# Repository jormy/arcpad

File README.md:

# arcpad

arcpad is a 11 key macropad with a rotary enccoder and a light bar.
made for Hack Club's Stardance Hackpad program.

## features

- snap fit 3d printed case with no screws needed
- 11 keys in a 4x3 layout
- EC11 rotary encoder
- light bar composed of 5 LEDS that can be programmed to show whatever you want (e.g. volume, brightness)
- QMK firmware with VIA support (not tested yet)

## CAD model

I wanted to keep the design really compact, so I decided not to use screws and secured the PCB with friction instead.

The PCB is sandwiched between a base and a top plate, the PCB is secured to the top plate when the switches are attached, and the top plate secures to the base with some neat snap fit geometry

All parts of the model are printable with no supports, with exception of the USB-C opening in the base.

## PCB

here are the schematic andn PCB designs, both made in Kicad:

## Firmware

This macropad uses QMK firmware. It has VIA support, though I will need to test it when I make the physical macropad.

## BOM

everything you need to make this macropad

- 11x Cherry MX Switches
- 11x DSA Keycaps
- 12x through-hole 1N4148 Diodes
- 16x SK6812 MINI-E LEDs
- 1x EC11 Rotary encoder
- 1x XIAO RP2040
- 1x 100 µF capacitor
- 1x 330Ω resistor
- 1x Case (3 3d printed parts)

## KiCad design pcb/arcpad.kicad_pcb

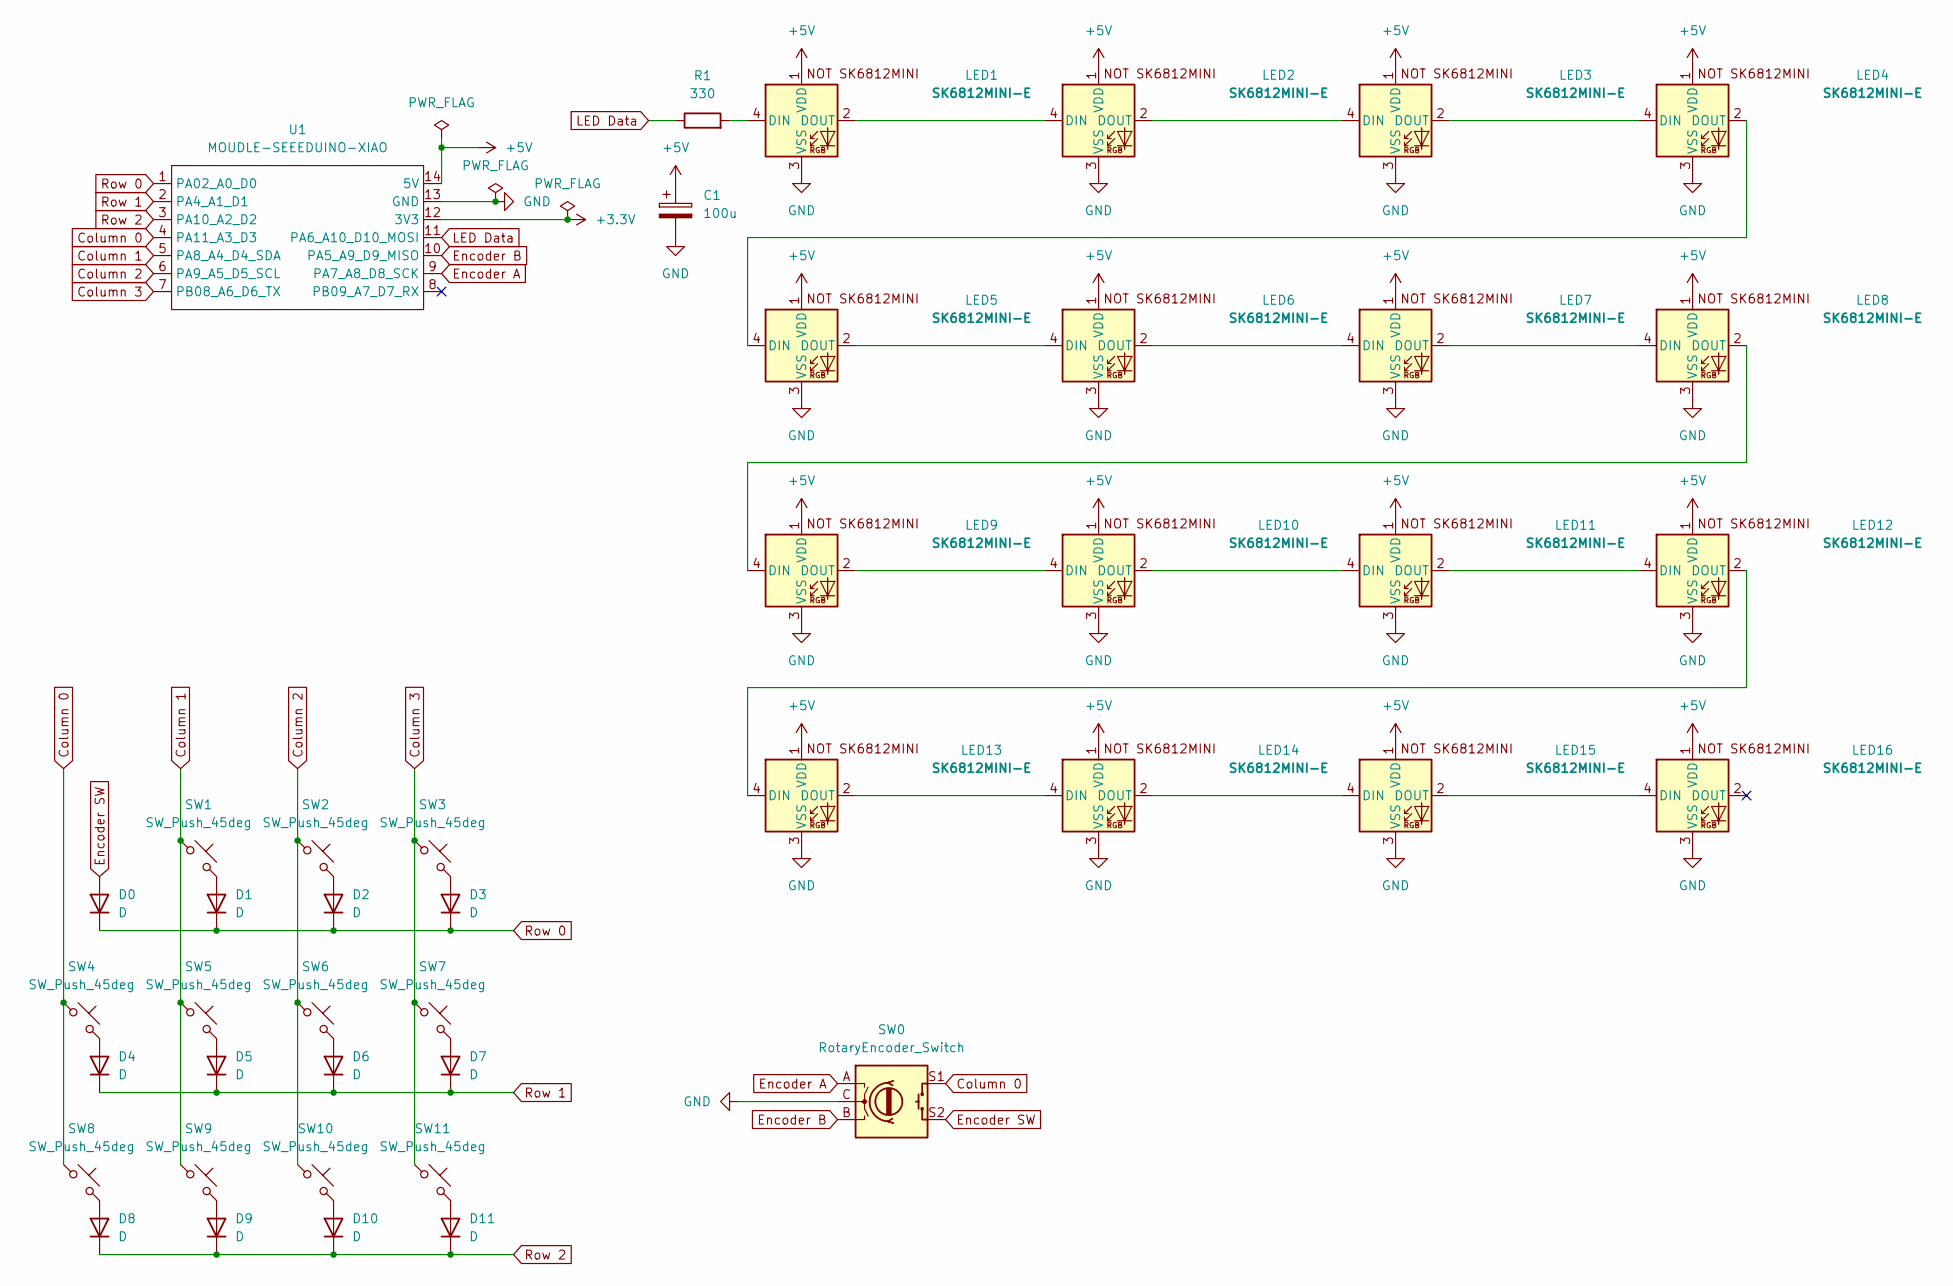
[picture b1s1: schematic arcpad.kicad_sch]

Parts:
C1: 100u; CP_Radial_D5.0mm_P2.00mm
D0, D1, D2, D3, D4, D5, D6, D7, D8, D9, D10, D11: D; D_DO-35_SOD27_P7.62mm_Horizontal
LED1, LED2, LED3, LED4, LED5, LED6, LED7, LED8, LED9, LED10, LED11, LED12, LED13, LED14, LED15, LED16: SK6812MINI-E; SK6812MINI-E_fixed
R1: 330; R_Axial_DIN0207_L6.3mm_D2.5mm_P7.62mm_Horizontal
SW0: RotaryEncoder_Switch; RotaryEncoder_Alps_EC11E-Switch_Vertical_H20mm
SW1, SW2, SW3, SW4, SW5, SW6, SW7, SW8, SW9, SW10, SW11: SW_Push_45deg; SW_Cherry_MX_1.00u_PCB
U1: MOUDLE-SEEEDUINO-XIAO; XIAO-Generic-Hybrid-14P-2.54-21X17.8MM

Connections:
+3.3V: U1.12 (3V3)
+5V: C1.1, LED1.1 (VDD), LED2.1 (VDD), LED3.1 (VDD), LED4.1 (VDD), LED5.1 (VDD), LED6.1 (VDD), LED7.1 (VDD), LED8.1 (VDD), LED9.1 (VDD), LED10.1 (VDD), LED11.1 (VDD), LED12.1 (VDD), LED13.1 (VDD), LED14.1 (VDD), LED15.1 (VDD), LED16.1 (VDD), U1.14 (5V)
Column 0: SW0.S1, SW4.1, SW8.1, U1.4 (PA11_A3_D3)
Column 1: SW1.1, SW5.1, SW9.1, U1.5 (PA8_A4_D4_SDA)
Column 2: SW2.1, SW6.1, SW10.1, U1.6 (PA9_A5_D5_SCL)
Column 3: SW3.1, SW7.1, SW11.1, U1.7 (PB08_A6_D6_TX)
Encoder A: SW0.A, U1.9 (PA7_A8_D8_SCK)
Encoder B: SW0.B, U1.10 (PA5_A9_D9_MISO)
Encoder SW: D0.2 (A), SW0.S2
GND: C1.2, LED1.3 (VSS), LED2.3 (VSS), LED3.3 (VSS), LED4.3 (VSS), LED5.3 (VSS), LED6.3 (VSS), LED7.3 (VSS), LED8.3 (VSS), LED9.3 (VSS), LED10.3 (VSS), LED11.3 (VSS), LED12.3 (VSS), LED13.3 (VSS), LED14.3 (VSS), LED15.3 (VSS), LED16.3 (VSS), SW0.C, U1.13 (GND)
LED Data: R1.1, U1.11 (PA6_A10_D10_MOSI)
unnamed: D1.2 (A), SW1.2
unnamed: D2.2 (A), SW2.2
unnamed: D3.2 (A), SW3.2
unnamed: D4.2 (A), SW4.2
unnamed: D5.2 (A), SW5.2
unnamed: D6.2 (A), SW6.2
unnamed: D7.2 (A), SW7.2
unnamed: D8.2 (A), SW8.2
unnamed: D9.2 (A), SW9.2
unnamed: D10.2 (A), SW10.2
unnamed: D11.2 (A), SW11.2
unnamed: LED1.4 (DIN), R1.2
unnamed: LED1.2 (DOUT), LED2.4 (DIN)
unnamed: LED2.2 (DOUT), LED3.4 (DIN)
unnamed: LED3.2 (DOUT), LED4.4 (DIN)
unnamed: LED4.2 (DOUT), LED5.4 (DIN)
unnamed: LED5.2 (DOUT), LED6.4 (DIN)
unnamed: LED6.2 (DOUT), LED7.4 (DIN)
unnamed: LED7.2 (DOUT), LED8.4 (DIN)
unnamed: LED8.2 (DOUT), LED9.4 (DIN)
unnamed: LED9.2 (DOUT), LED10.4 (DIN)
unnamed: LED10.2 (DOUT), LED11.4 (DIN)
unnamed: LED11.2 (DOUT), LED12.4 (DIN)
unnamed: LED12.2 (DOUT), LED13.4 (DIN)
unnamed: LED13.2 (DOUT), LED14.4 (DIN)
unnamed: LED14.2 (DOUT), LED15.4 (DIN)
unnamed: LED15.2 (DOUT), LED16.4 (DIN)
Row 0: D0.1 (K), D1.1 (K), D2.1 (K), D3.1 (K), U1.1 (PA02_A0_D0)
Row 1: D4.1 (K), D5.1 (K), D6.1 (K), D7.1 (K), U1.2 (PA4_A1_D1)
Row 2: D8.1 (K), D9.1 (K), D10.1 (K), D11.1 (K), U1.3 (PA10_A2_D2)

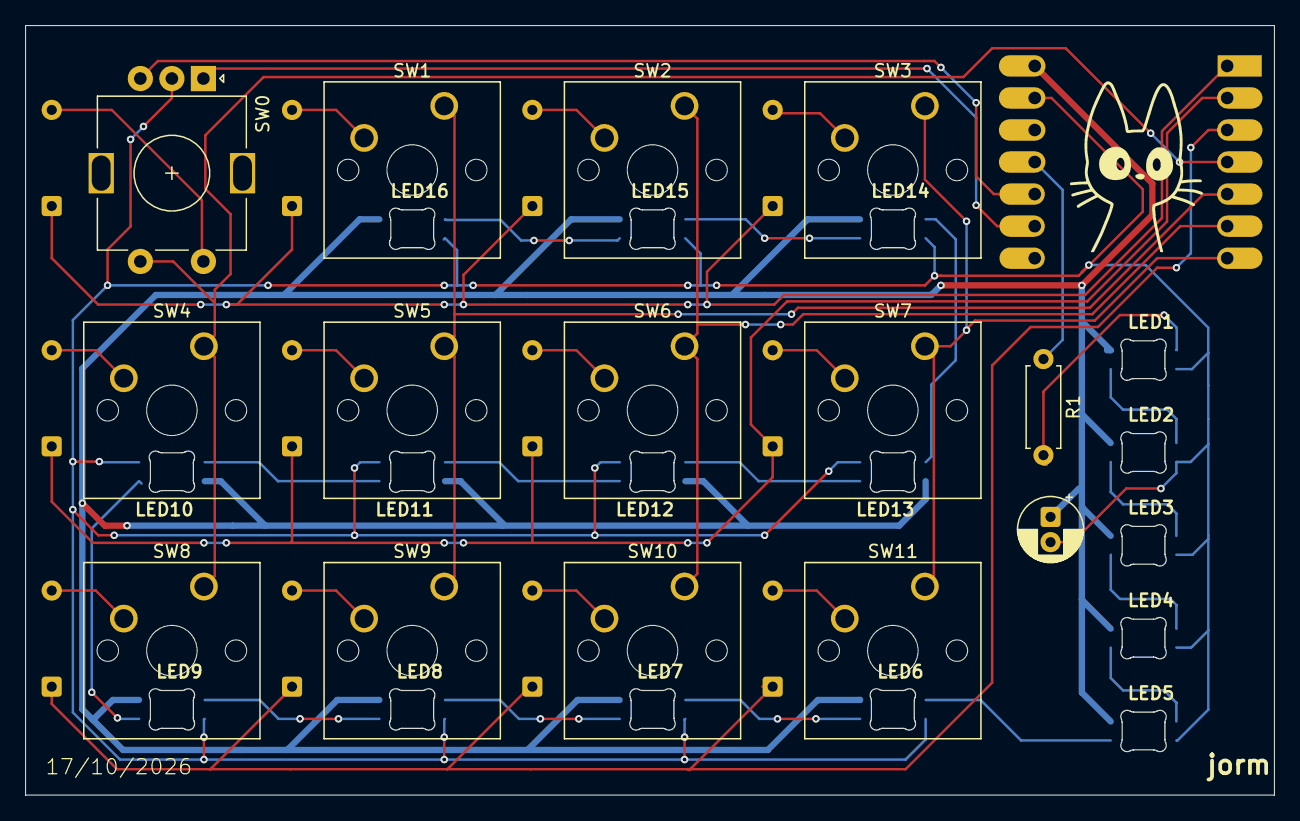
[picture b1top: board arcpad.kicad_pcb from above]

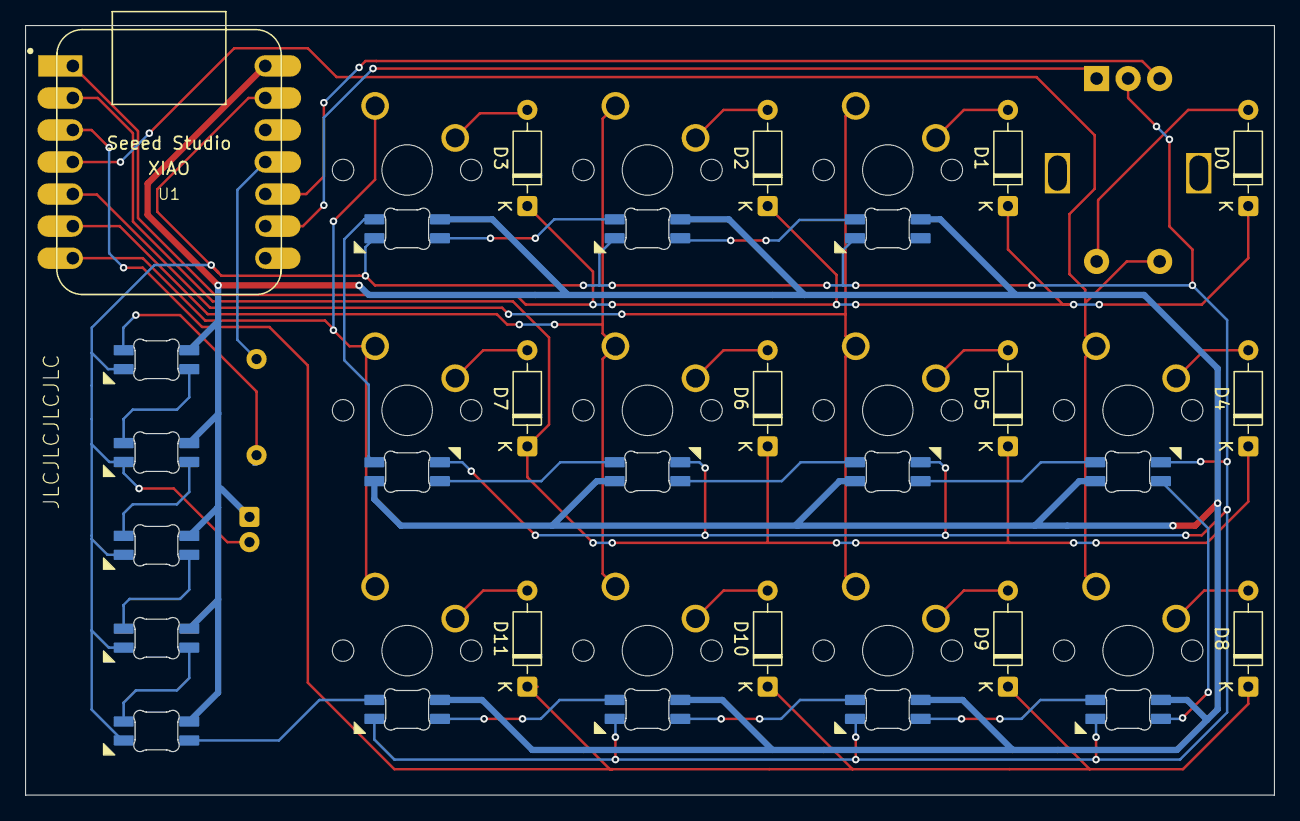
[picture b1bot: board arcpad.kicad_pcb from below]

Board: 2 copper layers, 99.0 x 61.0 mm, 43 parts (13 on the bottom side), 40 nets.
